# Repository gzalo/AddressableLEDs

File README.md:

# AddressableLEDs
Driver for WS2812 addressable LEDs. Supports different light effects, and OSC to sync with music beats (planned)

## PCB folder
This folder contains a PCB for a simple addressable LED driver board (based on an ATmega8). It can be opened with the free version of Eagle.

## UC folder
This folder contains the microcontroller code that acts as a bridge between the LED strip and the computer. The microcontroller is connected to a PC using a cheap USB-TTL converter (it must be able to support 256000 bps, so a modern converter is needed, such as cp2102, pl2303, ft232rl).

## PC folder
This folder contains the C++ code that can be used to send patterns to the LEDs. It can be compiled under Linux or Windows, and sends data directly to a serial port. OSC control is planned, not yet implemented.

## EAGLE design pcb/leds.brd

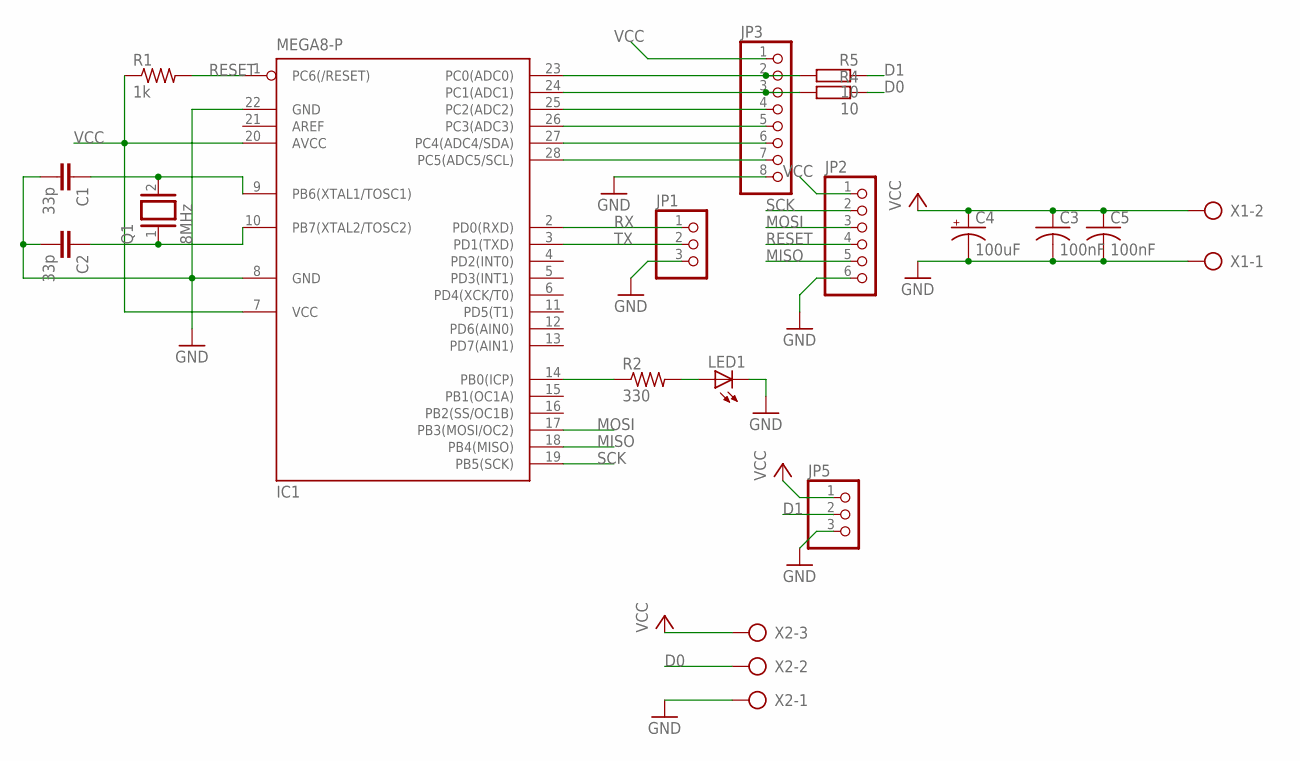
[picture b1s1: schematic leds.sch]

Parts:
C1, C2: 33p; C025-025X050
C3, C5: 100nF; C0805
C4: 100uF; E5-8,5
IC1: MEGA8-P; DIL28-3
JP1, JP5: PINHD-1X3; 1X03
JP2: PINHD-1X6; 1X06
JP3: PINHD-1X8; 1X08
LED1: LED3MM
Q1: 8MHz; QS
R1: 1k; M0805
R2: 330; M0805
R4, R5: 10; 0204/7
X1: AK500/2
X2: AK500/3

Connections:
D0: R4.1, X2.2
D1: JP5.2, R5.1
GND: C1.2, C2.2, C3.2, C4.-, C5.2, IC1.8 (GND), IC1.22 (GND), JP1.3, JP2.6, JP3.8, JP5.3, LED1.K (C), X1.1, X2.1
MISO: IC1.18 (PB4(MISO)), JP2.5
MOSI: IC1.17 (PB3(MOSI/OC2)), JP2.3
unnamed: IC1.27 (PC4(ADC4/SDA)), JP3.6
unnamed: IC1.23 (PC0(ADC0)), JP3.2, R5.2
unnamed: C1.1, IC1.9 (PB6(XTAL1/TOSC1)), Q1.2
unnamed: C2.1, IC1.10 (PB7(XTAL2/TOSC2)), Q1.1
unnamed: IC1.24 (PC1(ADC1)), JP3.3, R4.2
unnamed: IC1.25 (PC2(ADC2)), JP3.4
unnamed: IC1.26 (PC3(ADC3)), JP3.5
unnamed: IC1.28 (PC5(ADC5/SCL)), JP3.7
unnamed: IC1.14 (PB0(ICP)), R2.1
unnamed: LED1.A, R2.2
RESET: IC1.1 (PC6(/RESET)), JP2.4, R1.2
RX: IC1.2 (PD0(RXD)), JP1.1
SCK: IC1.19 (PB5(SCK)), JP2.2
TX: IC1.3 (PD1(TXD)), JP1.2
VCC: C3.1, C4.+, C5.1, IC1.7 (VCC), IC1.20 (AVCC), JP2.1, JP3.1, JP5.1, R1.1, X1.2, X2.3

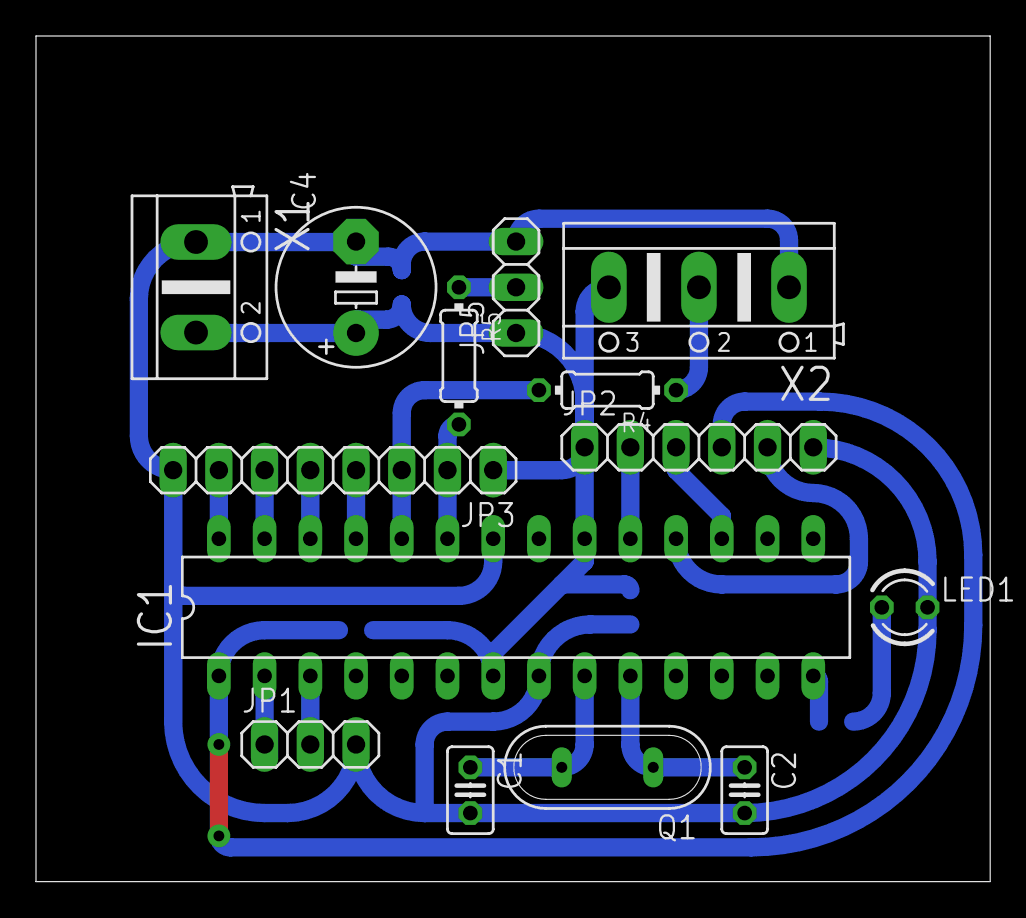
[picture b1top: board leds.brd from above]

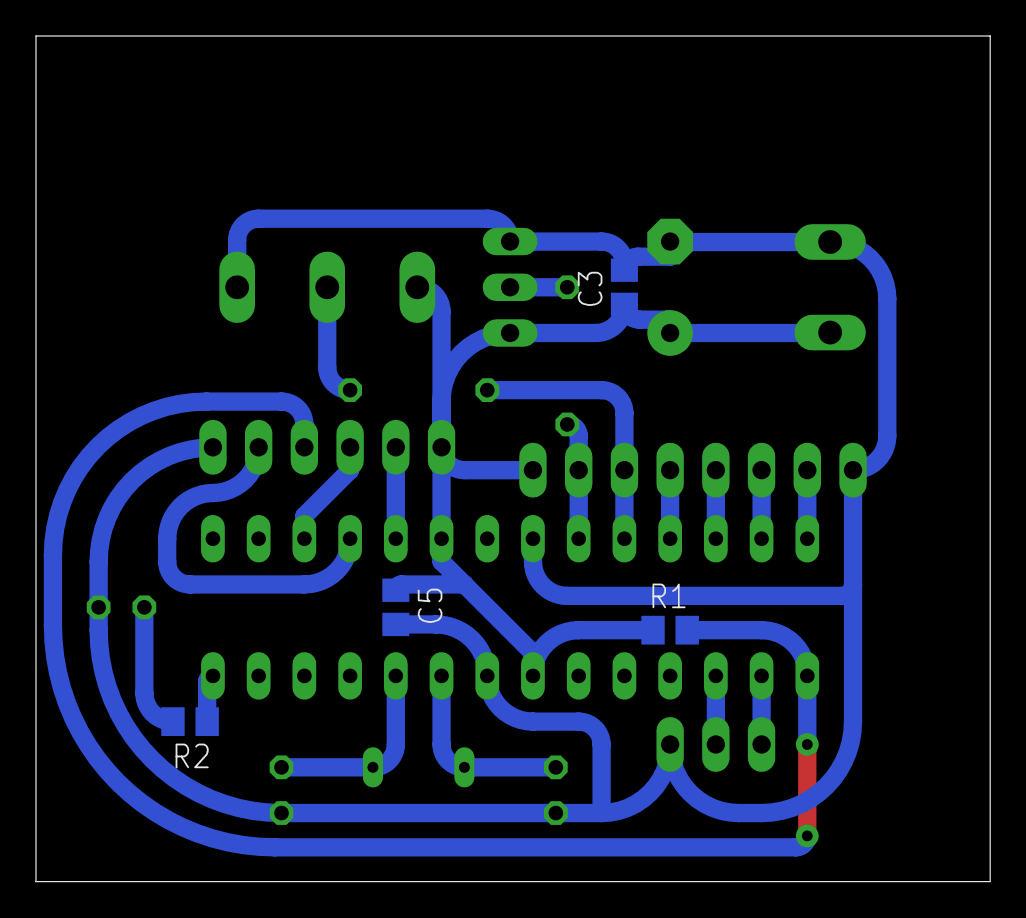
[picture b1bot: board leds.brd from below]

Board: 2 copper layers, 53.0 x 47.0 mm, 18 parts (4 on the bottom side), 20 nets.

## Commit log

2018-02-16 Inifial commit, readme, uc code and pcb
2018-02-16 PC software initial commit
